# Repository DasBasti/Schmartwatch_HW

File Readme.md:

# Schmart Watch Hardware

## Table of Contents

- [Introduction](#introduction)
- [Terms of Use](#terms-of-use)
- [Problems?](#problems)
- [Changelog](#changelog)

## Introduction

This application is the hardware for the DIY Smartwatch project [Schmart Watch](http://www.kurzschluss-blog.de/2018/07/schmartwatch-01-smartwatch-selbst-gebaut.html).

To open the project you need [KiCad Version 5.0.0-rc2](http://kicad-pcb.org/) or newer.

## Terms of Use

Refer to "License.txt" for terms of use.

## Problems?

If you have any problems or questions, please ensure you have read this readme
file. If you are still having trouble, you can
[get in contact](https://plus.google.com/+BastianNeumann_DasBasti).

## Changelog

1. 2018-07-15: Version 0.1
  - Initial release of hardware version E3

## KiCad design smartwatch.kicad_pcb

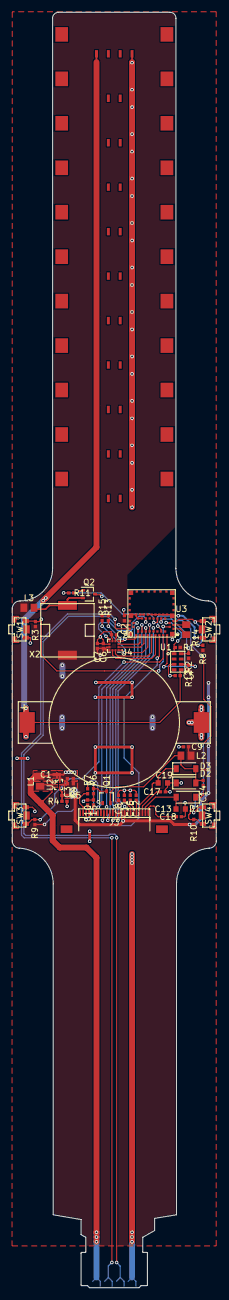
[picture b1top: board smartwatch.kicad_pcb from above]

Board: 2 copper layers, 34.4 x 215.2 mm, 66 parts (1 on the bottom side), 52 nets.

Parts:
C1, C3, C4, C6, C7: 10u/4V; R_0402_1005Metric_fixed
C2, C5, C8: 100n/6.3V; R_0402_1005Metric_fixed
C9, C14: 4.7u/6.3V; R_0402_1005Metric_fixed
C10, C11, C12, C15, C16, C17, C18: 1u/35; R_0402_1005Metric_fixed
C13, C19: 1u/50V; C_0603_1608Metric
C20: 22n/6.3V; R_0402_1005Metric_fixed
D1, D2, D3: MBR0530; D_SOD-123
J1: 505148-0408
J2, J2#2, J2#3, J2#4, J2#5, J2#6, J2#7, J2#8, J2#9, J2#10, J2#11: 505147-0490; 505147-0490_NO_SOLDER
J3: 505110-2491; MOLEX_FPC_24_P0.5mm_505110-2491
L1, L3: 2u2/650mA; L_0805_2012Metric
L2: 10u/520mA; L_0805_2012Metric
Q1, Q2: Si1308EDL; SOT-323_SC-70
R1, R2, R3, R7, R8, R9, R10, R11, R12, R13, R15: 10k; R_0402_1005Metric_fixed
R4, R6: 3R; R_0402_1005Metric_fixed
R5: R; R_0402_1005Metric_fixed
R14: R; R_0805_2012Metric
SW1, SW2, SW3, SW4: SKTDLDE010
U1: M41T62LC6F; LCC-8_1.5x3.2mm_P0.9mm
U2: TPS610994; BGA-6_2x3_1.0x1.35mm
U3: ISP1507-AX
U4: LSM303AGR; LGA-12_2x2mm_P0.5mm
X1: SMTU2032-LF; SMTU2032-LF-6066
X2: SMT-0940-T-3V-R; SMT-0940-T_3V-R

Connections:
+3V3: C2.1, C3.1, C4.1, C6.1, C7.1, C8.1, C9.1, J3.15, J3.16, L2.1, L3.1, R1.1, R2.1, R3.1, R5.1, R8.1, R9.1, R10.1, R12.1, R13.1, R15.1, U2.B2, U3.26, U4.9, U4.10, X2.1
+BATT: C5.1, J2.4, J2#2.4, J2#3.4, J2#4.4, J2#5.4, J2#6.4, J2#7.4, J2#8.4, J2#9.4, J2#10.4, J2#11.4, U1.5, X1.1
+VDC: C1.1, J1.1, L1.1, U2.A1, U2.C1
-BATT: C1.2, C2.2, C3.2, C4.2, C5.2, C6.2, C7.2, C8.2, C9.2, C10.2, C11.2, C12.2, C13.2, C15.2, C16.2, C17.2, C18.2, C19.2, C20.2, D2.1, J1.4, J2.1, J2#2.1, J2#3.1, J2#4.1, J2#5.1, J2#6.1, J2#7.1, J2#8.1, J2#9.1, J2#10.1, J2#11.1, J3.17, Q2.3, R4.2, R6.2, SW1.2, SW2.1, SW3.1, SW4.2, U1.3, U2.A2, U3.1, U3.7, U3.8, U3.10, U3.12, U3.14, U3.16, U3.18, U3.21, U3.23, U3.24, U3.25, U3.31, U4.6, U4.8, X1.2
/BRACE_CLOSED_IN: J2#2.2, J2#3.2, J2#4.2, J2#5.2, J2#6.2, J2#7.2, J2#8.2, J2#9.2, J2#10.2, J2#11.2
/BS: J3.8, U3.27
/BUSY: J3.9, U3.44
/BUZZER: R11.2, U3.13
/CS_MAG: U3.34, U4.3
/CS_XL: U3.36, U4.2
/D~C: J3.11, U3.35
/GDR: J3.2, R7.2
/INT_1_XL: U3.40, U4.12
/INT_2_XL: U3.42, U4.11
/INT_MAG: U3.19, U4.7
/INT_RTC: R12.2, U1.6, U3.48
/PREVGH: C19.1, D3.1, J3.21
/PREVGL: C13.1, D1.2, J3.23
/RESE: J3.3, Q1.3, R6.1
/SCLK: J3.13, U3.39
/SCL_IMU: R15.2, U3.38, U4.1
/SCL_RTC: R2.2, U1.8, U3.11
/SDA_IMU: R13.2, U3.32, U4.4
/SDA_RTC: R1.2, U1.1, U3.5
/SDI: J3.14, U3.41
/SWDCLK: J1.2, U3.30
/SWDIO: J1.3, U3.28
/SWNO: R8.2, SW2.2, U3.6
/SWNW: R3.2, SW1.1, U3.3
/SWSO: R10.2, SW4.1, U3.45
/SWSW: R9.2, SW3.2, U3.46
/VCOM: C18.1, J3.24
/VDD: C11.1, J3.18
/VGH: C15.1, J3.5
/VGL: C10.1, J3.4
/VPP: C16.1, J3.19
/VSH: C12.1, J3.20
/VSL: C17.1, J3.22
/~CS: J3.12, U3.37
/~RES: J3.10, U3.33
unnamed: C14.1, D1.1
unnamed: C14.2, D2.2, D3.2, L2.2, Q1.2
unnamed: C20.1, U4.5
unnamed: J2.3, J2#2.3, J2#3.3, J2#4.3, J2#5.3, J2#6.3, J2#7.3, J2#8.3, J2#9.3, J2#10.3, J2#11.3
unnamed: L1.2, U2.B1
unnamed: L3.2, Q2.2, X2.2
unnamed: Q1.1, R7.1
unnamed: Q2.1, R11.1
unnamed: R4.1, R5.2, U2.C2
unnamed: R14.1, U3.2
unnamed: R14.2, U3.4
unnamed: U3.20, U3.22

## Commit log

2018-07-15 Initial commit of HW Version E3
2018-07-15 Added Readme.md and License.txt
